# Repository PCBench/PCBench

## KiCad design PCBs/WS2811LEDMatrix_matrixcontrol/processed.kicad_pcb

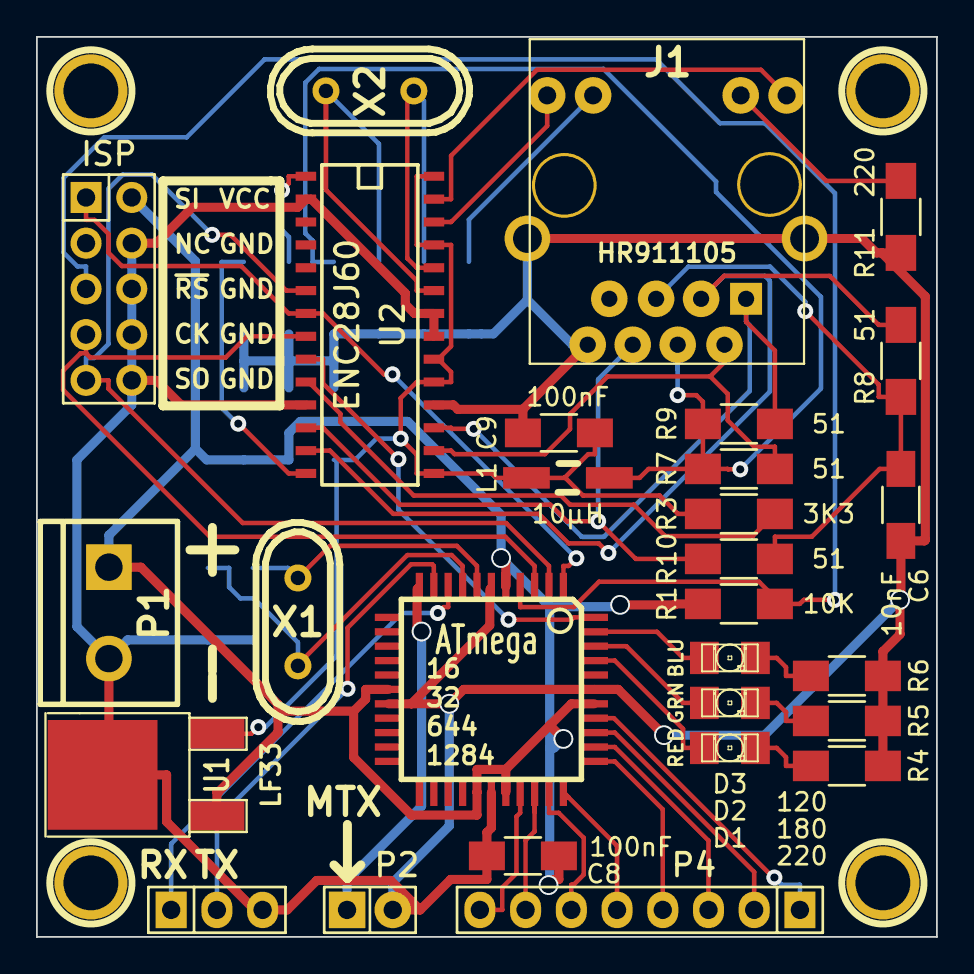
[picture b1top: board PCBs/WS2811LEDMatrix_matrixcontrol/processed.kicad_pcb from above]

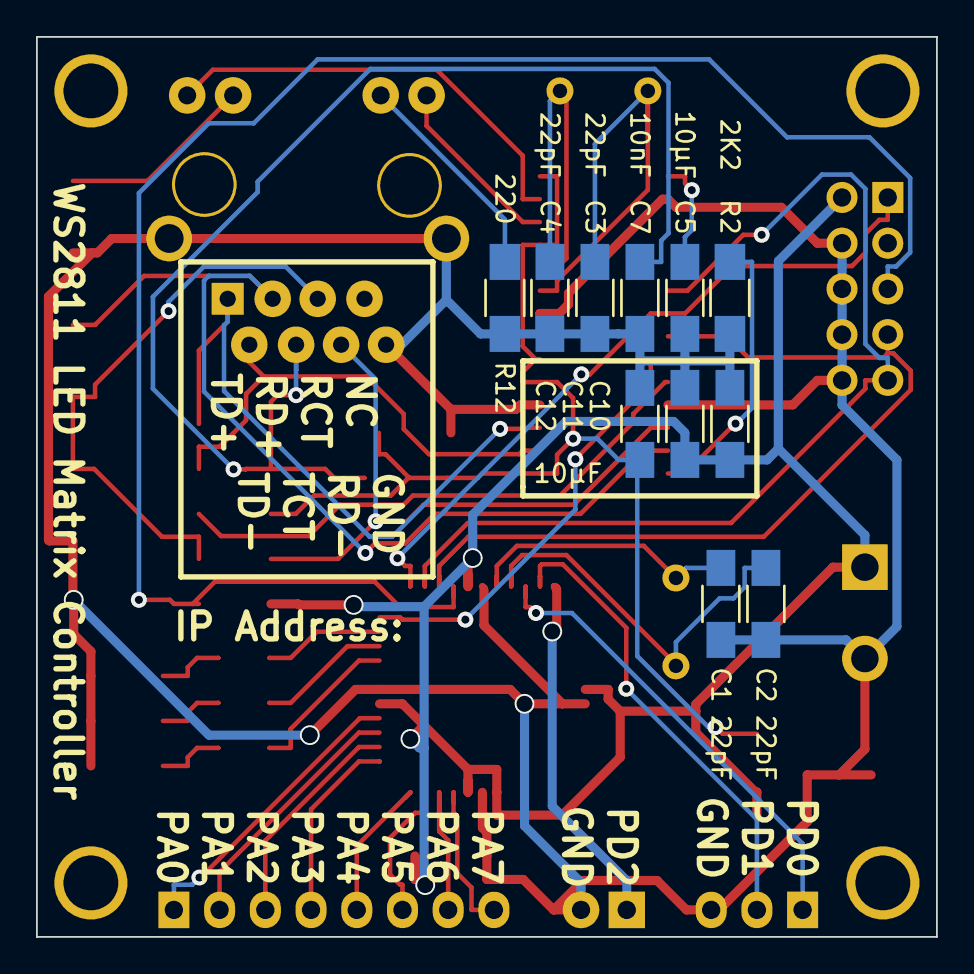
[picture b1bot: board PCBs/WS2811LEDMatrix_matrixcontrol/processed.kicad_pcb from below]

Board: 2 copper layers, 50.0 x 50.0 mm, 43 parts (11 on the bottom side), 42 nets.

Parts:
C1, C2, C3, C4: 22pF; C_1206_HandSoldering
C5, C10, C11, C12: 10µF; C_1206_HandSoldering
C6, C7: 10nF; C_1206_HandSoldering
C8, C9: 100nF; C_1206_HandSoldering
D1: RED; LED-1206
D2: GRN; LED-1206
D3: BLU; LED-1206
IC1: ATmega; TQFP-44
ISP: ISP; Pin_Header_Straight_2x05
J1: HR911105; HR911105_RJ45
L1: 10µH; Choke_SMD_1206_Handsoldering
MOUNT1, MOUNT2, MOUNT3, MOUNT4: 1pin
P1: POWER_IN; bornier2
P2: MATRIX DATA; Pin_Header_Straight_1x02
P3: SERIAL; Pin_Header_Straight_1x03
P4: CONN_01X08; Pin_Header_Straight_1x08
R1: 10K; R_1206_HandSoldering
R2: 2K2; R_1206_HandSoldering
R3: 3K3; R_1206_HandSoldering
R4, R11, R12: 220; R_1206_HandSoldering
R5: 180; R_1206_HandSoldering
R6: 120; R_1206_HandSoldering
R7, R8, R9, R10: 51; R_1206_HandSoldering
U1: LF33; DPAK-2
U2: ENC28J60; SOIC-28
X1: 16MHz; Crystal_HC49-U_Vertical
X2: 25MHz; Crystal_HC49-U_Vertical

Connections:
+5V: C8.1, C10.1, C11.1, IC1.5, IC1.17, IC1.27, IC1.29, IC1.38, ISP.2, P1.1, R1.1, U1.1
/MISO: IC1.2, ISP.9, U2.6
/MOSI: IC1.1, ISP.1, U2.7
/MTX_DAT: IC1.11, P2.1
/RXD: IC1.9, P3.1
/SCK: IC1.3, ISP.7, U2.8
/STATLED1: D1.1, IC1.41
/STATLED2: D2.1, IC1.42
/STATLED3: D3.1, IC1.43
/TXD: IC1.10, P3.2
/~RESET: IC1.4, ISP.5, R1.2
GND: C1.2, C2.2, C3.2, C4.2, C5.2, C6.2, C7.2, C8.2, C9.2, C10.2, C11.2, C12.2, IC1.6, IC1.18, IC1.28, IC1.39, ISP.4, ISP.6, ISP.8, ISP.10, J1.0, J1.8, P1.2, P2.2, P3.3, R2.2, R4.1, R5.1, R6.1, R11.2, R12.2, U1.2, U2.2, U2.11, U2.18, U2.21, U2.22
unnamed: C1.1, IC1.7, X1.1
unnamed: C2.1, IC1.8, X1.2
unnamed: C3.1, U2.23, X2.1
unnamed: C4.1, U2.24, X2.2
unnamed: C5.1, U2.1
unnamed: C6.1, J1.5, R8.2, R10.2
unnamed: C7.1, J1.4, L1.2, R7.1, R9.1
unnamed: C9.1, C12.1, L1.1, R3.1, U1.3, U2.15, U2.19, U2.20, U2.25, U2.28
unnamed: D1.2, R4.2
unnamed: D2.2, R5.2
unnamed: D3.2, R6.2
unnamed: IC1.30, P4.8
unnamed: IC1.31, P4.7
unnamed: IC1.32, P4.6
unnamed: IC1.33, P4.5
unnamed: IC1.34, P4.4
unnamed: IC1.35, P4.3
unnamed: IC1.36, P4.2
unnamed: IC1.37, P4.1
unnamed: IC1.44, U2.9
unnamed: J1.1, R9.2, U2.17
unnamed: J1.2, R7.2, U2.16
unnamed: J1.3, R8.1, U2.13
unnamed: J1.6, R10.1, U2.12
unnamed: J1.9, U2.27
unnamed: J1.10, R11.1
unnamed: J1.11, R12.1
unnamed: J1.12, U2.26
unnamed: R2.1, U2.14
unnamed: R3.2, U2.10

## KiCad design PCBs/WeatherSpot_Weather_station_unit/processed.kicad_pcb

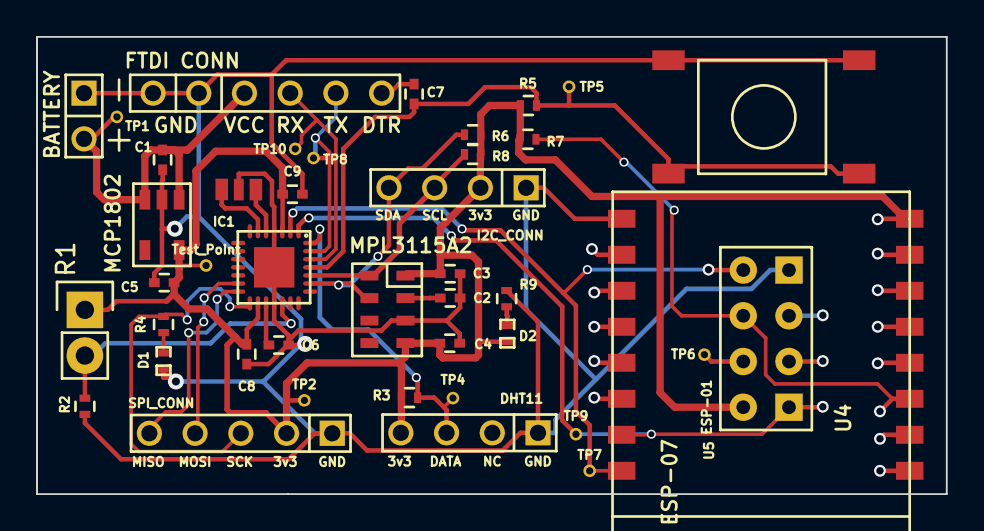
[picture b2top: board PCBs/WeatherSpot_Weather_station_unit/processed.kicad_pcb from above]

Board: 2 copper layers, 50.5 x 25.4 mm, 42 parts (0 on the bottom side), 24 nets.

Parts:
BT1: BATTERY; BATT_CONN
C1, C5: 1uF; C_0402
C2, C4: 100nF; C_0402
C3: 10uF; C_0402
C6, C7, C8, C9: 0.1uF; C_0402
D1, D2: LED; SMD-0402_LED
IC1: ATMEGA328P-MM; QFN-28-4x4mm_fixed_mask
P1: FTDI CONN; FTDI_PORT
Q1: Oscilator; ceramic_resonator_smd
R1: PhotoResistor; Socket_Strip_Straight_1x02
R2, R5, R7: 10K; R_0402
R3: 5K; R_0402
R4, R9: 470; R_0402
R6, R8: 4.7K; R_0402
SW1: SW_PUSH; push_switch_SMD
TP1: TP1; TEST_POINT
TP2: TP2; TEST_POINT
TP3: Test_Point; TEST_POINT
TP4: TP4; TEST_POINT
TP5: TP5; TEST_POINT
TP6: TP6; TEST_POINT
TP7: TP7; TEST_POINT
TP8: TP8; TEST_POINT
TP9: TP9; TEST_POINT
TP10: TP10; TEST_POINT
U1: MPL3115A2
U2: MCP1802; MCP1802T
U3: DHT11
U4: ESP-07
U5: ESP-01
conn1: I2C_CONN
conn2: SPI_CONN

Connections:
3V3: C3.1, C4.1, C5.1, C8.1, C9.1, D2.2, IC1.3, IC1.16, R1.1, R3.1, R5.1, R6.1, R7.1, R8.1, TP2.1, TP3.1, U1.1, U1.4, U2.5, U3.1, U4.8, U5.4, conn1.3, conn2.4
/D2: IC1.28, R3.2, TP4.1, U3.2
/DTR: C7.1, P1.6
/MISO: IC1.14, conn2.1
/MOSI: IC1.13, conn2.2
/RX: IC1.26, P1.4, TP10.1
/RXS: IC1.1, TP9.1, U4.15, U5.5
/SCK: IC1.15, R4.2, conn2.3
/TX: IC1.27, P1.5, TP8.1
/TXS: IC1.2, TP7.1, U4.16, U5.1
/VCC: BT1.1, C1.1, P1.3, TP1.1, U2.1, U2.3
A0: IC1.19, R1.2, R2.1
GND: BT1.2, C1.2, C2.2, C3.2, C4.2, C5.2, C6.2, C8.2, C9.2, D1.2, IC1.4, IC1.18, P1.1, P1.2, Q1.1, R2.2, R9.2, SW1.2, U1.3, U2.2, U3.4, U4.9, U5.8, conn1.4, conn2.5
unnamed: C2.1, U1.2
unnamed: C6.1, IC1.17
unnamed: C7.2, IC1.25, R5.2, SW1.1, TP5.1
unnamed: D1.1, R4.1
unnamed: D2.1, R9.1
unnamed: IC1.5, Q1.3
unnamed: IC1.6, Q1.2
unnamed: R7.2, U4.3, U5.2
unnamed: TP6.1, U5.3
SCL: IC1.24, R8.2, U1.8, conn1.2
SDA: IC1.23, R6.2, U1.7, conn1.1

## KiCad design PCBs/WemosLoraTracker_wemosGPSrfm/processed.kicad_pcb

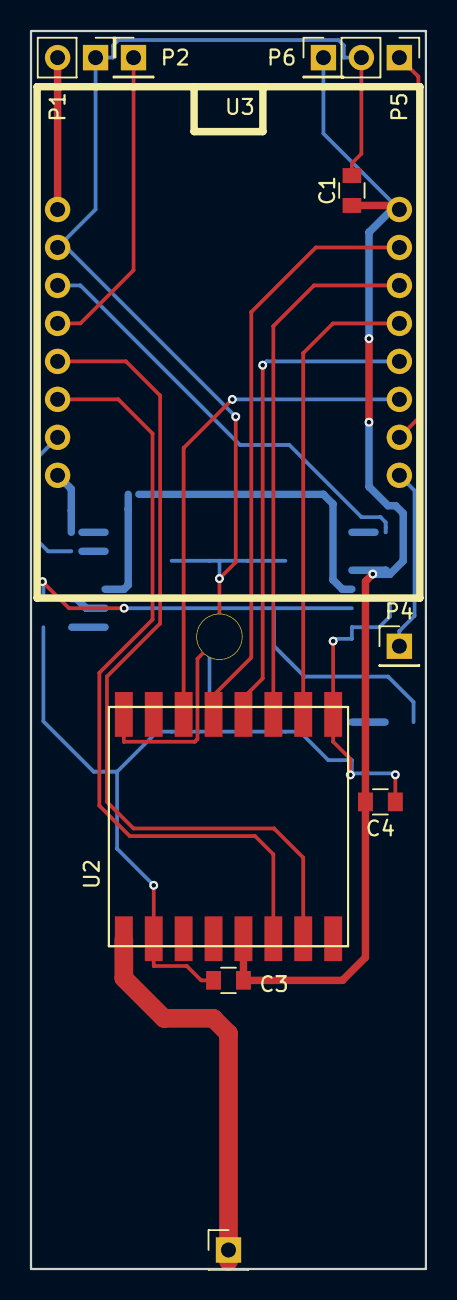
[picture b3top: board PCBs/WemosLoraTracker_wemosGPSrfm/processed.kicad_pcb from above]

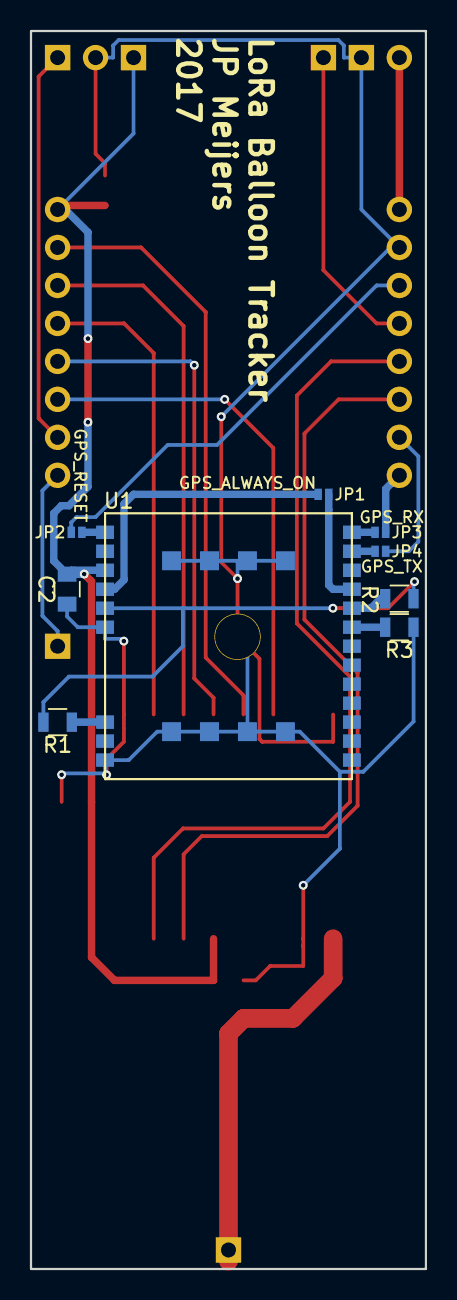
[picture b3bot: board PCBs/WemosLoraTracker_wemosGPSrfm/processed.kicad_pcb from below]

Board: 2 copper layers, 26.4 x 82.8 mm, 20 parts (9 on the bottom side), 26 nets.

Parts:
C1, C4: 10uF; C_0805
C2, C3: 100nF; C_0805
JP1: GPS_ALWAYS_ON; S_JUMPER_2
JP2: GPS_RESET; S_JUMPER_2
JP3: GPS_RX; S_JUMPER_2
JP4: GPS_TX; S_JUMPER_2
P1: BATTERY; Socket_Strip_Straight_1x02_Pitch2.54mm
P2: CONN_DIO0; Socket_Strip_Straight_1x01_Pitch2.54mm
P3, P6: CONN_01X01; Socket_Strip_Straight_1x01_Pitch2.54mm
P4: RESET; Socket_Strip_Straight_1x01_Pitch2.54mm
P5: ADC_INPUT; Socket_Strip_Straight_1x02_Pitch2.54mm
R1: 10k; R_0805
R2, R3: 2k2; R_0805
U1: GPS_A2235-H
U2: RFM95
U3: WEMOS_D1_mini

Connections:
/3V3: C1.1, C2.1, C3.1, C4.1, P6.1, U1.3, U2.13, U3.16
/5V: P1.2, U3.1
/ADC: P5.1, U3.10
/DIO0: P2.1, U3.4
/DIO1/TX: JP3.2, U3.8
/DIO2: JP2.2, U3.3
/DIO3/RX: JP4.2, U3.7
/DIO4/rfmDIO1: U2.15, U3.5
/DIO5/rfmDIO0: U2.14, U3.6
/DIO12/MISO: U2.2, U3.13
/DIO13/MOSI: U2.3, U3.14
/DIO14/SCK: U2.4, U3.12
/DIO15/SS: U2.5, U3.15
/DIO16/rfmRESET: U2.6, U3.11
/GND: C1.2, C2.2, C3.2, C4.2, P1.1, P5.2, R3.2, U1.6, U1.9, U1.23, U1.24, U1.25, U1.26, U1.27, U1.28, U1.29, U1.30, U1.31, U2.1, U2.8, U2.10, U3.2
/GPS_1V8: R1.1, R2.2, U1.5
/GPS_RESET: JP2.1, U1.1
/GPS_RX: JP3.1, U1.22
/GPS_TX: JP4.1, U1.21
/RST: P4.1, U3.9
unnamed: JP1.1, U1.4
unnamed: JP1.2, U1.19
unnamed: P3.1, U2.9
unnamed: R1.2, U1.7
unnamed: R2.1, U1.18
unnamed: R3.1, U1.17

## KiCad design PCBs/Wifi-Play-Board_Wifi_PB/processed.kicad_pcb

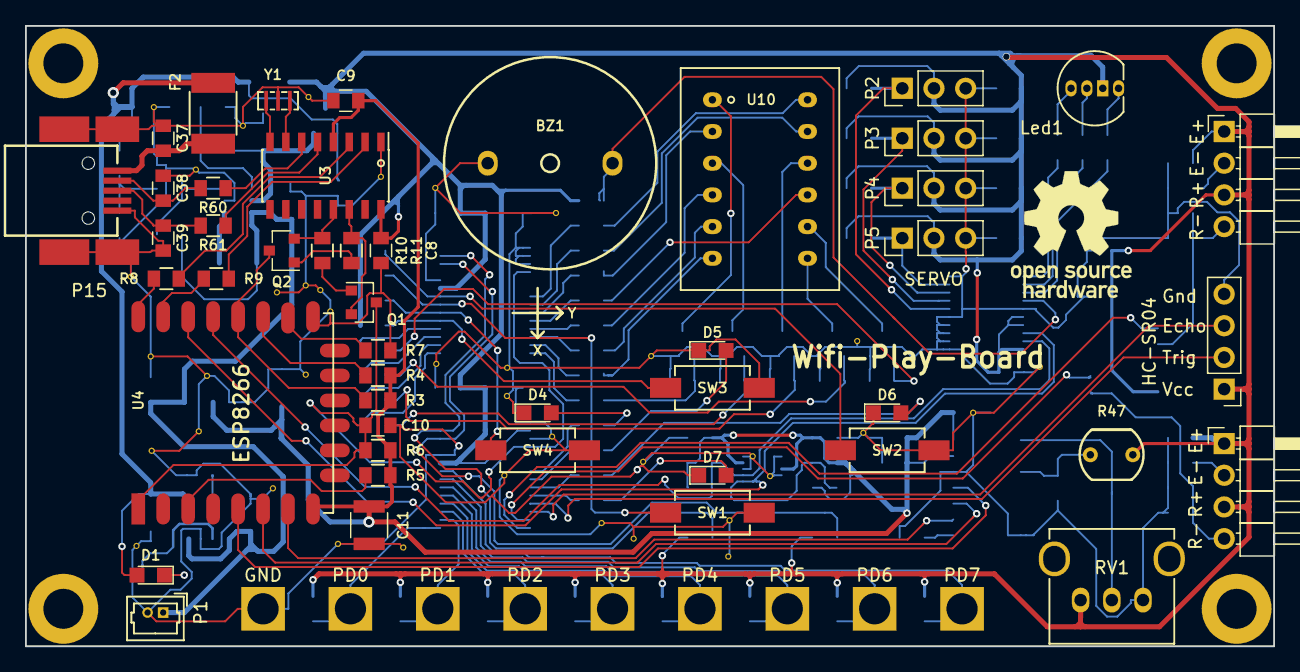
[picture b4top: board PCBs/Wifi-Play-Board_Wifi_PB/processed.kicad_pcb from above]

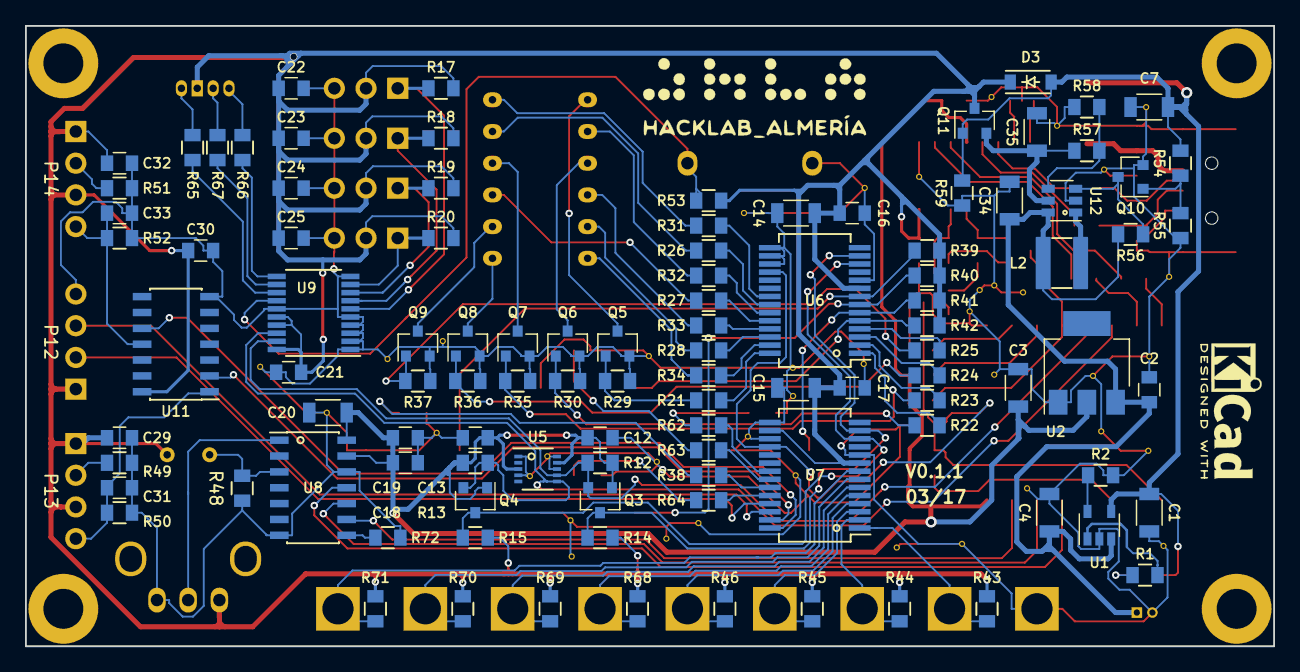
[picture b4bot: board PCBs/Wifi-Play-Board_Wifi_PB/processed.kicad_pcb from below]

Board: 2 copper layers, 100.0 x 49.7 mm, 200 parts (105 on the bottom side), 111 nets.

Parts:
BZ1: Buzzer; LOUDITY_LD-BZPN-1705
C1, C4, C14, C15, C20, C34: 4u7; C_1206
C2, C8, C9, C12, C13, C16, C17, C18, C19, C21, C29, C30, C32: 100n; C_0805
C3, C7, C35: 10u; C_1206
C10: 0.47n; C_0805
C11: 100u; C_1210
C22, C23, C24, C25: 1u; C_0805
C31, C33, C37: 10n; C_0805
C38, C39: 0,047n; C_0805
D1, D4, D5, D6, D7: LED; LED_0805
D3: MBR0520; SOD-123
F2: F; R_1812
Gnd-Via: VAL**; Gnd-Via
Gnd-Via_2, Gnd-Via_3, Gnd-Via_4, Gnd-Via_5, Gnd-Via_6, Gnd-Via_7, Gnd-Via_8, Gnd-Via_9, Gnd-Via_10, Gnd-Via_11, Gnd-Via_12, Gnd-Via_13, Gnd-Via_14, Gnd-Via_15, Gnd-Via_16, Gnd-Via_17, Gnd-Via_18, Gnd-Via_19, Gnd-Via_20, Gnd-Via_21, Gnd-Via_22, Gnd-Via_23, Gnd-Via_24, Gnd-Via_25, Gnd-Via_26, Gnd-Via_27, Gnd-Via_28, Gnd-Via_29, Gnd-Via_30, Gnd-Via_31, Gnd-Via_32, Gnd-Via_33, Gnd-Via_34, Gnd-Via_35, Gnd-Via_36, Gnd-Via_37, Gnd-Via_38, Gnd-Via_39: VAL**; Gnd-Via
L2: 4u7; BOURNS_SRN4012T
Led1: Led_RGB; LED_RGB_5mm_G_B_COM_R_Anodo_comun
P1: CONN_01X02; Molex_PicoBlade_53047-0210_02x1.25mm_Straight
P2, P3, P4, P5: CONN_01X03; Pin_Header_Straight_1x03_Pitch2.54mm
P6, P7, P8, P9, P10, P16, P17, P18, P19: CONN_01X01; Pad_Conector_Cocodrilo
P12: CONN_01X04; Socket_Strip_Straight_1x04_Pitch2.54mm
P13, P14: CONN_01X04; Pin_Header_Angled_1x04_Pitch2.54mm
P15: USB_MINI; usb_mini_molex_675031020
Q1, Q2, Q5, Q6, Q7, Q8, Q9: SMBT3904; SOT-23
Q3, Q4: BSS138; SOT-23
Q10: BC849; SOT-23
Q11: NX2301P; SOT-23
R1, R2, R8, R9: 470; R_0805
R3, R4, R5, R6, R7, R10, R11, R17, R18, R19, R20, R39, R40, R41, R42, R53, R56, R59: 10K; R_0805
R12, R13, R14, R15: 4K7; R_0805
R21, R22, R23, R24, R25, R48, R54: 1K; R_0805
R26, R27, R28, R31, R32, R33, R34, R65, R66, R67: 120; R_0805
R29, R30, R35, R36, R37, R50, R52, R55, R72: 47K; R_0805
R38, R62, R63, R64: 220; R_0805
R43, R44, R45, R46, R68, R69, R70, R71: 10M; R_0805
R47: LDR; LDR_TOKEN_PGM5_Series
R49, R51: 220R; R_0805
R57: 976K; R_0805
R58: 309K; R_0805
R60, R61: 22R; R_0805
RV1: POT; ALP_RK09K111
SW1, SW2, SW3, SW4: Pulsador_2p; CANAL_ELECTRONIC_DTSM-31N-B
U1: MCP73831T; SOT-23-5
U2: LD1117S33TR; SOT-223
U3: CH340G; SOIC-16_3.9x9.9mm_Pitch1.27mm
U4: ESP8266; ESP-12E
U5: MMA7660FC; DFN-10-1EP_3x3mm_Pitch0.5mm
U6, U7: MCP23017; SSOP-28_5.3x10.2mm_Pitch0.65mm
U8: MCP3204; SOIC-14_3.9x8.7mm_Pitch1.27mm
U9: PCA9634; TSSOP-20_4.4x6.5mm_Pitch0.65mm
U10: Matriz_5x7_Anodo_Filas; Matriz_Led_7X5
U11: 40106; SOIC-14_3.9x8.7mm_Pitch1.27mm
U12: MCP1640; SOT-23-6
Y1: Cristal; Murata_CSTCE_V_A

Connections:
+3V3: C3.1, C9.1, C11.1, C12.1, C13.1, C18.1, C19.1, C20.1, Q3.1, Q4.1, R3.2, R4.2, R5.2, R6.2, R12.1, R13.1, U2.2, U3.4, U4.8, U5.3, U5.9, U8.13, U8.14
+5V: C8.1, C14.1, C15.1, C16.1, C17.1, C21.1, C22.1, C23.1, C24.1, C25.1, C29.1, C30.1, C32.1, D3.1, Led1.3, P2.2, P3.2, P4.2, P5.2, P12.1, P13.1, P13.3, P14.1, P14.3, Q11.3, R14.1, R15.1, R17.1, R18.1, R19.1, R20.1, R39.1, R40.1, R41.1, R42.1, R43.1, R44.1, R45.1, R46.1, R47.1, R53.1, R68.1, R69.1, R70.1, R71.1, RV1.1, U3.16, U6.9, U7.9, U7.16, U9.16, U9.17, U9.20, U11.14
/Control/EN: R5.1, U4.3
/Control/GPIO0: Q2.3, R3.1, U4.18
/Control/GPIO2: R4.1, U4.17
/Control/GPIO15: R7.1, U4.16
/Control/RxD: R9.1, U4.21
/Control/TxD: R8.1, U4.22
/Control/USBD+: R61.1, U3.5
/Control/USBD-: R60.1, U3.6
BUZZER: BZ1.1, R53.2, U9.14
CH0: RV1.2, U8.1
CH2: R47.2, R48.2, U8.3
GND: BZ1.2, C1.2, C2.2, C3.2, C4.2, C7.2, C8.2, C9.2, C10.2, C11.2, C12.2, C13.2, C14.2, C15.2, C16.2, C17.2, C18.2, C19.2, C20.2, C21.2, C22.2, C23.2, C24.2, C25.2, C29.2, C30.2, C31.2, C32.2, C33.2, C34.2, C35.2, C37.2, C38.2, C39.2, D4.1, D5.1, D6.1, D7.1, Gnd-Via.1, Gnd-Via_2.1, Gnd-Via_3.1, Gnd-Via_4.1, Gnd-Via_5.1, Gnd-Via_6.1, Gnd-Via_7.1, Gnd-Via_8.1, Gnd-Via_9.1, Gnd-Via_10.1, Gnd-Via_11.1, Gnd-Via_12.1, Gnd-Via_13.1, Gnd-Via_14.1, Gnd-Via_15.1, Gnd-Via_16.1, Gnd-Via_17.1, Gnd-Via_18.1, Gnd-Via_19.1, Gnd-Via_20.1, Gnd-Via_21.1, Gnd-Via_22.1, Gnd-Via_23.1, Gnd-Via_24.1, Gnd-Via_25.1, Gnd-Via_26.1, Gnd-Via_27.1, Gnd-Via_28.1, Gnd-Via_29.1, Gnd-Via_30.1, Gnd-Via_31.1, Gnd-Via_32.1, Gnd-Via_33.1, Gnd-Via_34.1, Gnd-Via_35.1, Gnd-Via_36.1, Gnd-Via_37.1, Gnd-Via_38.1, Gnd-Via_39.1, P1.2, P2.3, P3.3, P4.3, P5.3, P10.1, P12.4, P15.5, P15.6, Q5.2, Q6.2, Q7.2, Q8.2, Q9.2, Q10.2, R2.2, R7.2, R29.2, R30.2, R35.2, R36.2, R37.2, R48.1, R49.2, R50.2, R51.2, R52.2, R55.2, R58.2, R59.1, R72.2, RV1.3, SW1.1, SW2.1, SW3.1, SW4.1, U1.2, U2.1, U3.1, U4.15, U5.1, U5.4, U5.8, U5.10, U6.10, U6.15, U6.16, U6.17, U7.10, U7.15, U7.17, U8.7, U8.12, U9.1, U9.2, U9.3, U9.4, U9.5, U9.10, U9.15, U11.7, U12.2, Y1.2
LED_BLUE: R67.2, U9.12
LED_GREEN: R66.2, U9.11
LED_RED: R65.2, U9.13
MISO: U4.6, U8.10
MOSI: U4.7, U8.9
unnamed: C31.1, P13.4, R50.1, U11.1
unnamed: C33.1, P14.4, R52.1, U11.11
unnamed: C37.1, F2.2, P15.1
unnamed: C38.1, P15.2, R60.2
unnamed: C39.1, P15.3, R61.2
unnamed: D1.1, R1.2
unnamed: D4.2, R62.2
unnamed: D5.2, R63.2
unnamed: D6.2, R38.2
unnamed: D7.2, R64.2
unnamed: L2.2, U12.1
unnamed: Led1.1, R66.1
unnamed: Led1.2, R67.1
unnamed: Led1.4, R65.1
unnamed: P13.2, R49.1
unnamed: P14.2, R51.1
unnamed: Q1.1, R10.1
unnamed: Q1.2, R11.2, U3.14
unnamed: Q2.1, R11.1
unnamed: Q2.2, R10.2, U3.13
unnamed: Q5.1, R21.1, R29.1
unnamed: Q5.3, U10.1
unnamed: Q6.1, R22.1, R30.1
unnamed: Q6.3, U10.3
unnamed: Q7.1, R23.1, R35.1
unnamed: Q7.3, U10.10
unnamed: Q8.1, R24.1, R36.1
unnamed: Q8.3, U10.7
unnamed: Q9.1, R25.1, R37.1
unnamed: Q9.3, U10.8
unnamed: Q10.1, R54.1, R55.1
unnamed: Q10.3, R56.1, U12.3
unnamed: R1.1, U1.1
unnamed: R2.1, U1.5
unnamed: R8.2, U3.3
unnamed: R9.2, U3.2
unnamed: R26.1, U10.11
unnamed: R27.1, U10.9
unnamed: R28.1, U10.5
unnamed: R31.1, U10.12
unnamed: R32.1, U10.2
unnamed: R33.1, U10.4
unnamed: R34.1, U10.6
unnamed: R57.2, R58.1, U12.4
unnamed: R72.1, U8.8
unnamed: U3.7, Y1.1
unnamed: U3.8, Y1.3
PA0: R31.2, U6.21
PA1: R26.2, U6.22
PA2: R32.2, U6.23
PA3: R27.2, U6.24
PA4: R33.2, U6.25
PA5: R28.2, U6.26
PA6: R34.2, U6.27
PA7: R21.2, U6.28
PB0: R22.2, U6.1
PB1: R23.2, U6.2
PB2: R24.2, U6.3
PB3: R25.2, U6.4
PB4: R42.2, SW3.2, U6.5
PB5: R41.2, SW4.2, U6.6
PB6: R40.2, SW1.2, U6.7
PB7: R39.2, SW2.2, U6.8
PC0: R62.1, U7.21
PC1: R63.1, U7.22
PC2: R38.1, U7.23
PC3: R64.1, U7.24
PC4: P12.2, U7.25
PC5: P12.3, U7.26
PC6: U7.27, U11.2
PC7: U7.28, U11.10
PD0: P6.1, R43.2, U7.1
PD1: P7.1, R44.2, U7.2
PD2: P8.1, R45.2, U7.3
PD3: P9.1, R46.2, U7.4
PD4: P16.1, R68.2, U7.5
PD5: P17.1, R69.2, U7.6
PD6: P18.1, R70.2, U7.7
PD7: P19.1, R71.2, U7.8
SCK: U4.5, U8.11
SCL: Q4.2, R13.2, U4.20, U5.6, U9.18
SCL2: Q4.3, R15.2, U6.12, U7.12
SDA: Q3.2, R12.2, U4.19, U5.7, U9.19
SDA2: Q3.3, R14.2, U6.13, U7.13
SERVO1: P2.1, R17.2, U9.6
SERVO2: P3.1, R18.2, U9.7
SERVO3: P4.1, R19.2, U9.8
SERVO4: P5.1, R20.2, U9.9
V5VBOOST: C35.1, Q11.2, R57.1, U12.5
VBATT: C2.1, C4.1, C34.1, L2.1, P1.1, R56.2, U1.3, U2.3, U12.6
VUSB: C1.1, C7.1, D1.2, D3.2, F2.1, Q11.1, R54.2, R59.2, U1.4
~RESET: C10.1, Q1.3, R6.1, U4.1, U6.18, U7.18

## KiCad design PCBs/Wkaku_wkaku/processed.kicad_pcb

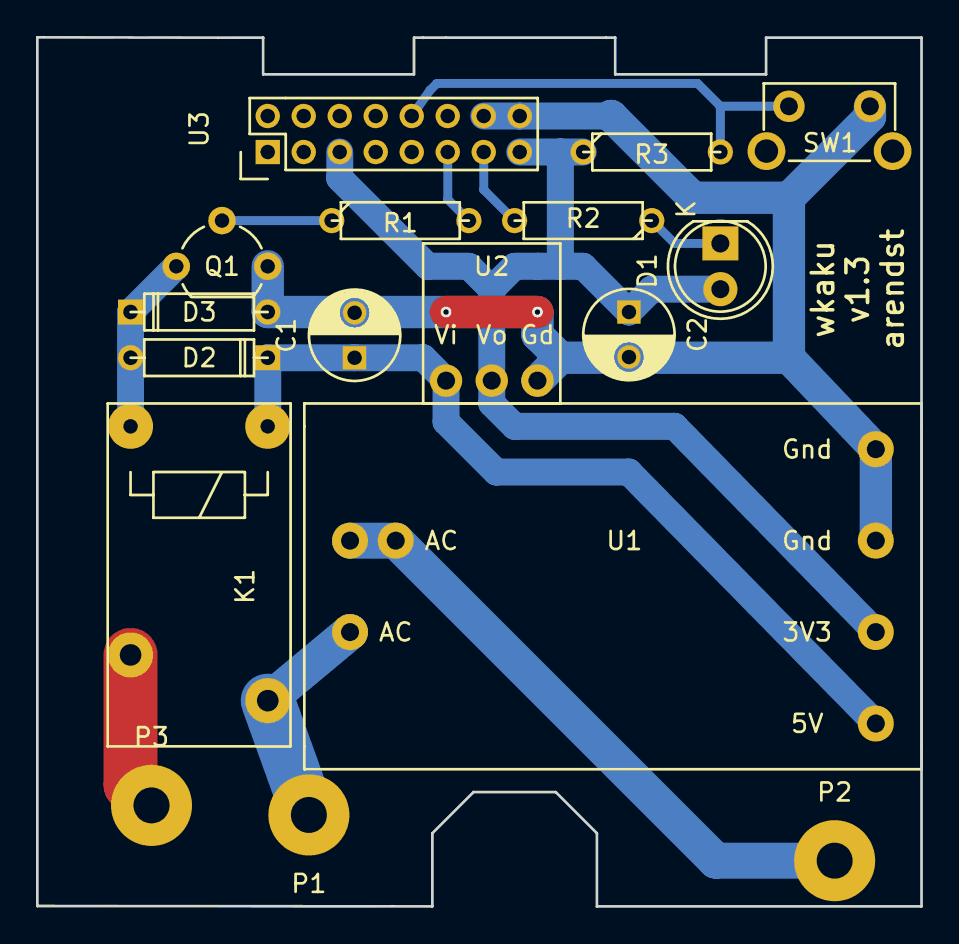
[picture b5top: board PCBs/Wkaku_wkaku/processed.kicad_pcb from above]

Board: 2 copper layers, 49.1 x 48.3 mm, 17 parts (0 on the bottom side), 12 nets.

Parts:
C1, C2: 100uF; C_Radial_D5_L11_P2.5
D1: LED; LED-5MM
D2, D3: 1N4007; D3
K1: RELAY_SPST; Relay_SPST
P1: Li; SolderWirePad_single_2mmDrill
P2: N; SolderWirePad_single_2mmDrill
P3: Lo; SolderWirePad_single_2mmDrill
Q1: BC547; TO-92_Molded_Wide
R1, R2: 1k; R3
R3: 10k; R3
SW1: SPST; SW_Tactile_SPST_Angled
U1: ACDC_Opt2; ACDC_Options
U2: AMS1117
U3: ESP-12E; ESP-12_Pitch2.00mm

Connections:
+3V3: C2.1, D1.2, R3.1, U1.4, U2.2, U3.3, U3.8
+5V: C1.1, D2.1, K1.A1, U1.3, U2.3
/BUTTON: R3.2, SW1.1, U3.18
/LED: R2.2, U3.7
/LIFE: K1.7, P1.1, U1.1
/RELAY: R1.2, U3.6
GND: C1.2, C2.2, D3.2, Q1.3, SW1.2, U1.5, U1.6, U2.1, U3.15, U3.16
unnamed: D1.1, R2.1
unnamed: D2.2, D3.1, K1.A2, Q1.1
unnamed: K1.5, P3.1
unnamed: P2.1, U1.2, U1.7
unnamed: Q1.2, R1.1

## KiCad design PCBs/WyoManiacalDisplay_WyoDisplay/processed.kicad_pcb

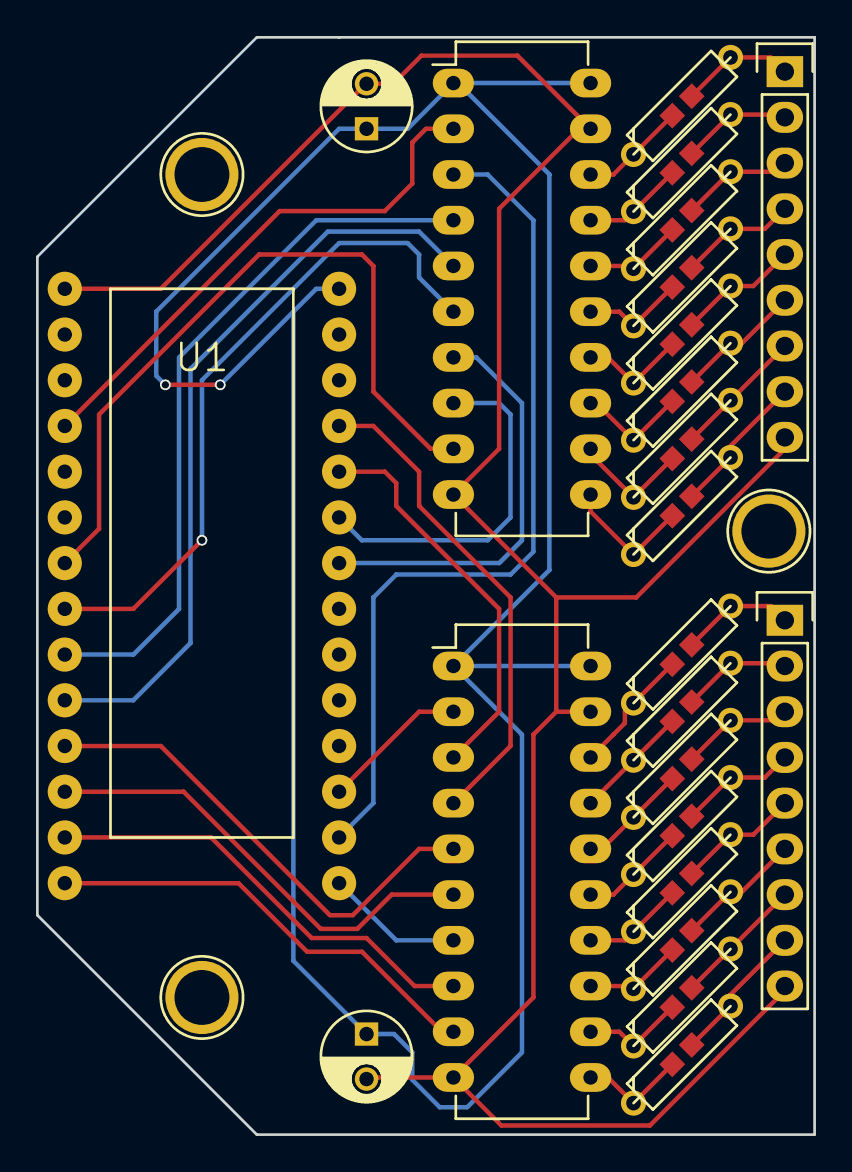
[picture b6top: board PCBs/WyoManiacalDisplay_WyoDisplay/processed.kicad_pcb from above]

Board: 2 copper layers, 43.2 x 61.0 mm, 23 parts (0 on the bottom side), 50 nets.

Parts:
C1, C2: 0.1uF; C_Radial_D5_L6_P2.5
P1: OUT1; Socket_Strip_Straight_1x09
P2: OUT2; Socket_Strip_Straight_1x09
R1, R2, R3, R4, R5, R6, R7, R8, R9, R10, R11, R12, R13, R14, R15, R16: R_Small; R-1-8w
U1: Teensy_3.1; Teensy-3.1
U2, U3: 74HCT245; DIP-20_W7.62mm_LongPads

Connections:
2: U1.2, U2.2
5: U1.5, U2.9
6: U1.6, U2.6
7: U1.7, U2.4
8: U1.8, U2.5
9: U1.9, U3.5
10: U1.10, U3.6
11: U1.11, U3.8
12: U1.12, U3.9
13: U1.13, U3.7
14: U1.14, U2.3
15: U1.15, U3.2
20: U1.20, U2.7
21: U1.21, U2.8
22: U1.22, U3.3
23: U1.23, U3.4
GND: C1.2, C2.2, P1.9, P2.9, U1.27, U2.10, U2.19, U3.10, U3.19
unnamed: P1.1, R1.2
unnamed: P1.2, R2.2
unnamed: P1.3, R3.2
unnamed: P1.4, R4.2
unnamed: P1.5, R5.2
unnamed: P1.6, R6.2
unnamed: P1.7, R7.2
unnamed: P1.8, R8.2
unnamed: P2.1, R9.2
unnamed: P2.2, R10.2
unnamed: P2.3, R11.2
unnamed: P2.4, R12.2
unnamed: P2.5, R13.2
unnamed: P2.6, R14.2
unnamed: P2.7, R15.2
unnamed: P2.8, R16.2
unnamed: R1.1, U2.18
unnamed: R2.1, U2.17
unnamed: R3.1, U2.16
unnamed: R4.1, U2.15
unnamed: R5.1, U2.14
unnamed: R6.1, U2.13
unnamed: R7.1, U2.12
unnamed: R8.1, U2.11
unnamed: R9.1, U3.18
unnamed: R10.1, U3.17
unnamed: R11.1, U3.16
unnamed: R12.1, U3.15
unnamed: R13.1, U3.14
unnamed: R14.1, U3.13
unnamed: R15.1, U3.12
unnamed: R16.1, U3.11
VCC: C1.1, C2.1, U1.26, U2.1, U2.20, U3.1, U3.20

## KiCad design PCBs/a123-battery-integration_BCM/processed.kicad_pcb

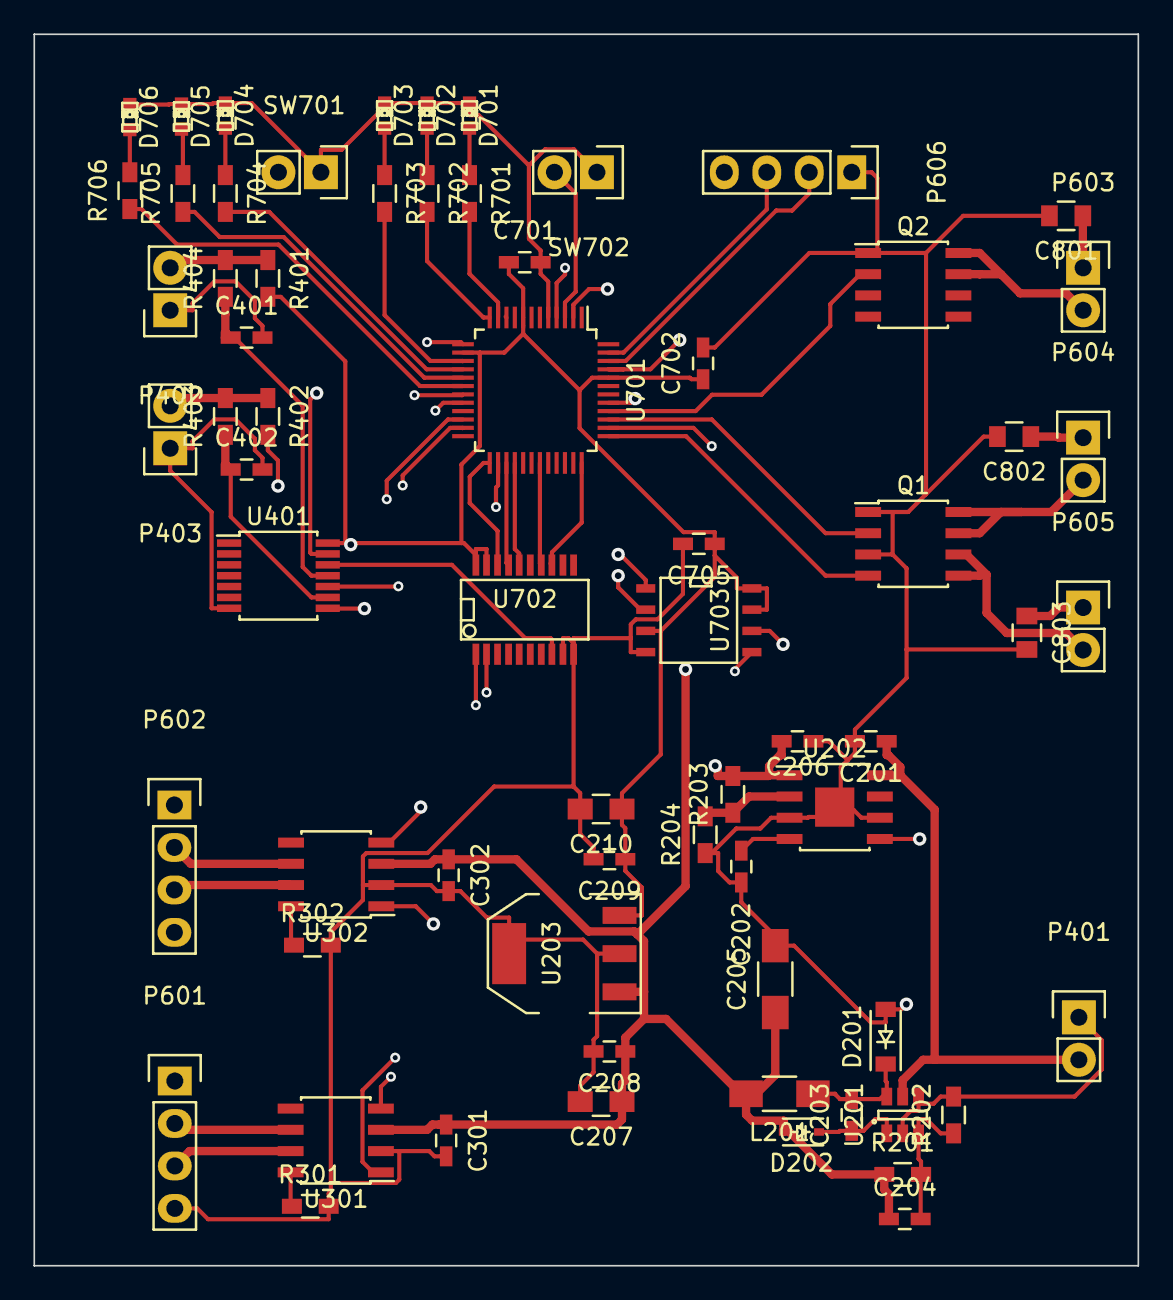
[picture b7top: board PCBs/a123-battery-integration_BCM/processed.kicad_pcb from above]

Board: 4 copper layers, 66.0 x 73.7 mm, 67 parts (0 on the bottom side), 59 nets.

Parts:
C201, C206, C401, C402: 1uF; C_0603_HandSoldering
C202: 10nF; C_0603_HandSoldering
C203: 0.22pF; C_0603_HandSoldering
C204: 10pF; C_0603_HandSoldering
C205: 100uF; C_1206_HandSoldering
C207, C210: 10u; C_0805_HandSoldering
C208, C209, C701, C702: 100n; C_0603_HandSoldering
C301, C302, C705: 0.1uF; C_0603_HandSoldering
C801, C802, C803: 10uF; C_0805
D201: MBR0540; SOD-123
D202: CMDSH-3; SOD-323
D701, D702, D703, D704, D705, D706: RED; LED-0603
L201: 47uH; C_1206_HandSoldering
P401: POWERCON; Pin_Header_Straight_1x02
P402: KEYSWITCH; Pin_Header_Straight_1x02
P403: CHARGESW; Pin_Header_Straight_1x02
P601: BRUSA_CANCON; Pin_Header_Straight_1x04
P602: A123_CANCON; Pin_Header_Straight_1x04
P603: CON+; Pin_Header_Straight_1x02
P604: CON-; Pin_Header_Straight_1x02
P605: CONPRE; Pin_Header_Straight_1x02
P606: UART; Pin_Header_Straight_1x04
Q1, Q2: IRF7101PbF; SOIC-8_3.9x4.9mm_Pitch1.27mm
R201: 1M; R_0603_HandSoldering
R202: 604K; R_0603_HandSoldering
R203: 88.7k; R_0603_HandSoldering
R204: 10k; R_0603_HandSoldering
R301, R302: 33k; R_0603_HandSoldering
R401, R402, R403, R404: 20k; R_0603_HandSoldering
R701, R702, R703, R704, R705, R706: 1k; R_0603_HandSoldering
SW701: ISP; Pin_Header_Straight_1x02
SW702: RESET; Pin_Header_Straight_1x02
U201: LT1934; SOT-23-6
U202: ADP7105; SOIC-8-1EP_3.9x4.9mm_Pitch1.27mm
U203: SPX2920M3-3.3; SOT-223
U301, U302: MCP2551-I/SN; SOIC-8_3.9x4.9mm_Pitch1.27mm
U401: 74LS14; TSSOP-14_4.4x5mm_Pitch0.65mm
U701: LPC11C14; LQFP-48_7x7mm_Pitch0.5mm
U702: MCP2515_TSSOP; SSOP-20
U703: AT25XX; SOIC-8-N

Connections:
+3V3: C209.1, C210.1, C701.1, C702.1, C705.1, R401.2, R402.2, U203.3, U401.14, U701.8, U701.14, U701.44, U702.19, U702.20, U703.3, U703.7, U703.8
+5V: C204.1, C205.1, C207.1, C208.1, C301.1, C302.1, D202.2, L201.2, P606.4, R201.1, U203.1, U301.3, U302.3
+12V: C206.1, P602.1, R203.1, U202.1
+15V: C201.1, C801.1, C802.1, C803.1, P401.2, P603.1, P604.1, P605.1, U201.5, U202.8
/Can transceiver/CAN1_H_I: P601.2, U301.6
/Can transceiver/CAN1_L_I: P601.3, U301.7
/Can transceiver/CAN1_RS: R301.1, U301.8
/Can transceiver/CAN1_RX: U301.4, U702.2
/Can transceiver/CAN1_TX: U301.1, U702.1
/Can transceiver/CAN2_H_I: P602.2, U302.6
/Can transceiver/CAN2_L_I: P602.3, U302.7
/Can transceiver/CAN2_RS: R302.1, U302.8
/Can transceiver/CAN2_RX: U302.4, U701.19
/Can transceiver/CAN2_TX: U302.1, U701.20
/Contactor Driver/CON+: Q2.2, U701.40
/Contactor Driver/CON+_LOW: P603.2, Q2.7, Q2.8
/Contactor Driver/CON-: Q1.2, U701.39
/Contactor Driver/CON-_LOW: P604.2, Q1.7, Q1.8
/Contactor Driver/CONPRE: Q1.4, U701.37
/Contactor Driver/CONPRE_LOW: P605.2, Q1.5, Q1.6
/Input Connectors/CHARGESWITCH_R: P403.2, R402.1, R403.2
/Input Connectors/CHARGESWITCH_RC: C402.1, R403.1, U401.9
/Input Connectors/KEYSKWITCH_RC: C401.1, R404.1, U401.11
/Input Connectors/KEYSWITCH_R: P402.2, R401.1, R404.2
/Power/5V0_BOOST: C203.1, D202.1, U201.1
/Power/5V0_FB: C204.2, R201.2, R202.1, U201.3
/Power/5V0_L: C203.2, D201.1, L201.1, U201.6
/Power/12V0_FB: R203.2, R204.1, U202.2
/Power/12V0_SS: C202.1, U202.4
/Power/EN12V0: U202.5, U701.45
/microController/CAN1_INT: U701.36, U702.13
/microController/CAN1_MISO: U701.27, U702.17
/microController/CAN1_MOSI: U701.28, U702.16
/microController/CAN1_SCK: U701.31, U702.14
/microController/CAN1_SSEL: U701.25, U702.18
/microController/CAN_OSC2: U401.12, U702.8
/microController/CHARGESWITCH_IN: U401.8, U701.22
/microController/CLKOUT: SW701.2, U401.13, U701.4
/microController/IO_LED0: R701.2, U701.11
/microController/IO_LED1: R702.2, U701.12
/microController/IO_LED2: R703.2, U701.15
/microController/IO_LED3: R704.2, U701.16
/microController/IO_LED4: R705.1, U701.17
/microController/IO_LED5: R706.1, U701.18
/microController/KEYSWITCH_IN: U401.10, U701.23
/microController/MCU_RESET: SW702.2, U701.3
/microController/MCU_RXD: P606.2, U701.46
/microController/MCU_TXD: P606.3, U701.47
/microController/PROM_MISO: U701.26, U703.2
/microController/PROM_MOSI: U701.38, U703.5
/microController/PROM_SCK: U701.13, U703.6
/microController/PROM_SSEL: U701.2, U703.1
GND: C201.2, C202.2, C205.2, C206.2, C207.2, C208.2, C209.2, C210.2, C301.2, C302.2, C401.2, C402.2, C701.2, C702.2, C705.2, C801.2, C802.2, C803.2, D201.2, D701.1, D702.1, D703.1, D704.1, D705.1, D706.1, P401.1, P402.1, P403.1, P601.4, P602.4, P606.1, Q1.1, Q1.3, Q2.1, R202.2, R204.2, R301.2, R302.2, SW701.1, SW702.1, U201.2, U201.4, U202.3, U202.6, U202.9, U203.2, U203.4, U301.2, U302.2, U401.7, U701.5, U701.41, U702.9, U702.10, U703.4
unnamed: D701.2, R701.1
unnamed: D702.2, R702.1
unnamed: D703.2, R703.1
unnamed: D704.2, R704.1
unnamed: D705.2, R705.2
unnamed: D706.2, R706.2
